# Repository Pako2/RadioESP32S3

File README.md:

# RadioESP32S3
## Introduction
&nbsp;&nbsp;&nbsp;&nbsp;Some time ago I published the [RadioESP32](https://github.com/Pako2/RadioESP32) project. It was intended exclusively for the basic ESP32 chips. I realized that it would be good to also try a variant with the more modern ESP32-S3 chip and this is the result. Since almost everything is identical to the original project, I will mainly emphasize the differences here.\
&nbsp;&nbsp;&nbsp;&nbsp;Complete project documentation can be found in the [UserGuide_EN.pdf](doc/UserGuide_EN.pdf) file.

## How to install
Experienced Tinkerers who have installed VS Code with PlatformIO supplement and normally use it probably do not need any other advice. Everything is described in the previous text. However, there may be some less experienced users who are interested in trying the project and do not need to make their own modifications. In this case, they can use pre-compiled binaries and install them in ESP32-S3 without VS Code/Platformio.
The procedure is as follows (valid only to Windows users):
1. The default assumption is that the development kit is connected to the USB port of your computer and you know the number of (virtual) COM port. Suppose it's a *COM10*. Use the connector marked *COM* (not *USB*) on the development kit.
2. Download the latest [RadioESP32S3_binaries.zip](https://github.com/Pako2/RadioESP32S3/releases/latest/download/RadioESP32S3_binaries.zip) and unpack the ZIP file to some suitable (work) folder.
3. In the selected folder, the **bin** folder appears that contains everything you need.
4. Open the command line window (**cmd.exe**) so that you are in the above folder **bin**.
5. Enter the **flash.bat** command. The following offer should appear:

6. Select the desired firmware version (ie press the appropriate number) and then press Enter.
7. You will then be prompted to enter a COM port. Write the corresponding name (by example in point **1** it would be *COM10*) and press Enter.
8. There should be installed the necessary SW into ESP32.
9. After completion you can continue according to the **First start** chapter.

<ins>Note:</ins>\
The *withota* and *withotanodisp* versions are intended for production use, while the *noota* and *nootanodisp* versions are intended primarily for the development phase (as they allow comfortable editing of web server files). However, there is nothing to prevent the *noota* and *nootanodisp* versions from being used for production use as well.

## First start
When the device is started for the first time, it runs in default settings and in AP mode. On the PC, connect to the **RadioESP32S3** network and in the browser to the address **192.168.4.1**. A web page should appear through which the device settings need to be made.

## Design of the device
The circuit diagram and printed circuit board were created using the Eagle design system.
### Wiring diagram

### Printed circuit board

## Choice of components
The basis of the design is the development kit "ESP32-S3-DevKitC-1" (shorter wider version). The board must have at least 8MB of flash memory and 4MB of PSRAM memory.

## Choice of GPIO
I designed and used a PCB where the assignment of GPIOs for various functions is therefore fixed. But this is not fixed in the software. In fact, it is the opposite, most GPIOs can be selected by the user, so it should be easy to use a different connection than the PCB I designed.
However, there are two exceptions:
1. Display connection - this must be set in the *platformio.ini* file before compilation.
2. Selection of ADC channel for battery measurement (I chose channel adc1-6, which corresponds to GPIO 7)

<ins>Note:</ins>\
In the original design with the ESP32 base chip, there is a third exception - connecting an SD card in SD_MMC mode. Fortunately, there is no such exception here, because in this case (ESP32-S3 chip) any GPIO pin can be used. This is of course a huge advantage, because the problems that were with the ESP32 base chip (there GPIO2, which is one of the bootstrapping pins, had to be used) have disappeared.

## Assembled board
Finally, you can see a few pictures of the printed circuit board completely assembled and including the installed subboards (ESP32 development kit and DAC). I also added one photo of the finished radio (without the cover).

### License
The code parts written by the author of the **RadioESP32S3** project are licensed under [GPL-3.0](LICENSE), 3rd party libraries that are used by this project are licensed under different license schemes, please check them out as well.

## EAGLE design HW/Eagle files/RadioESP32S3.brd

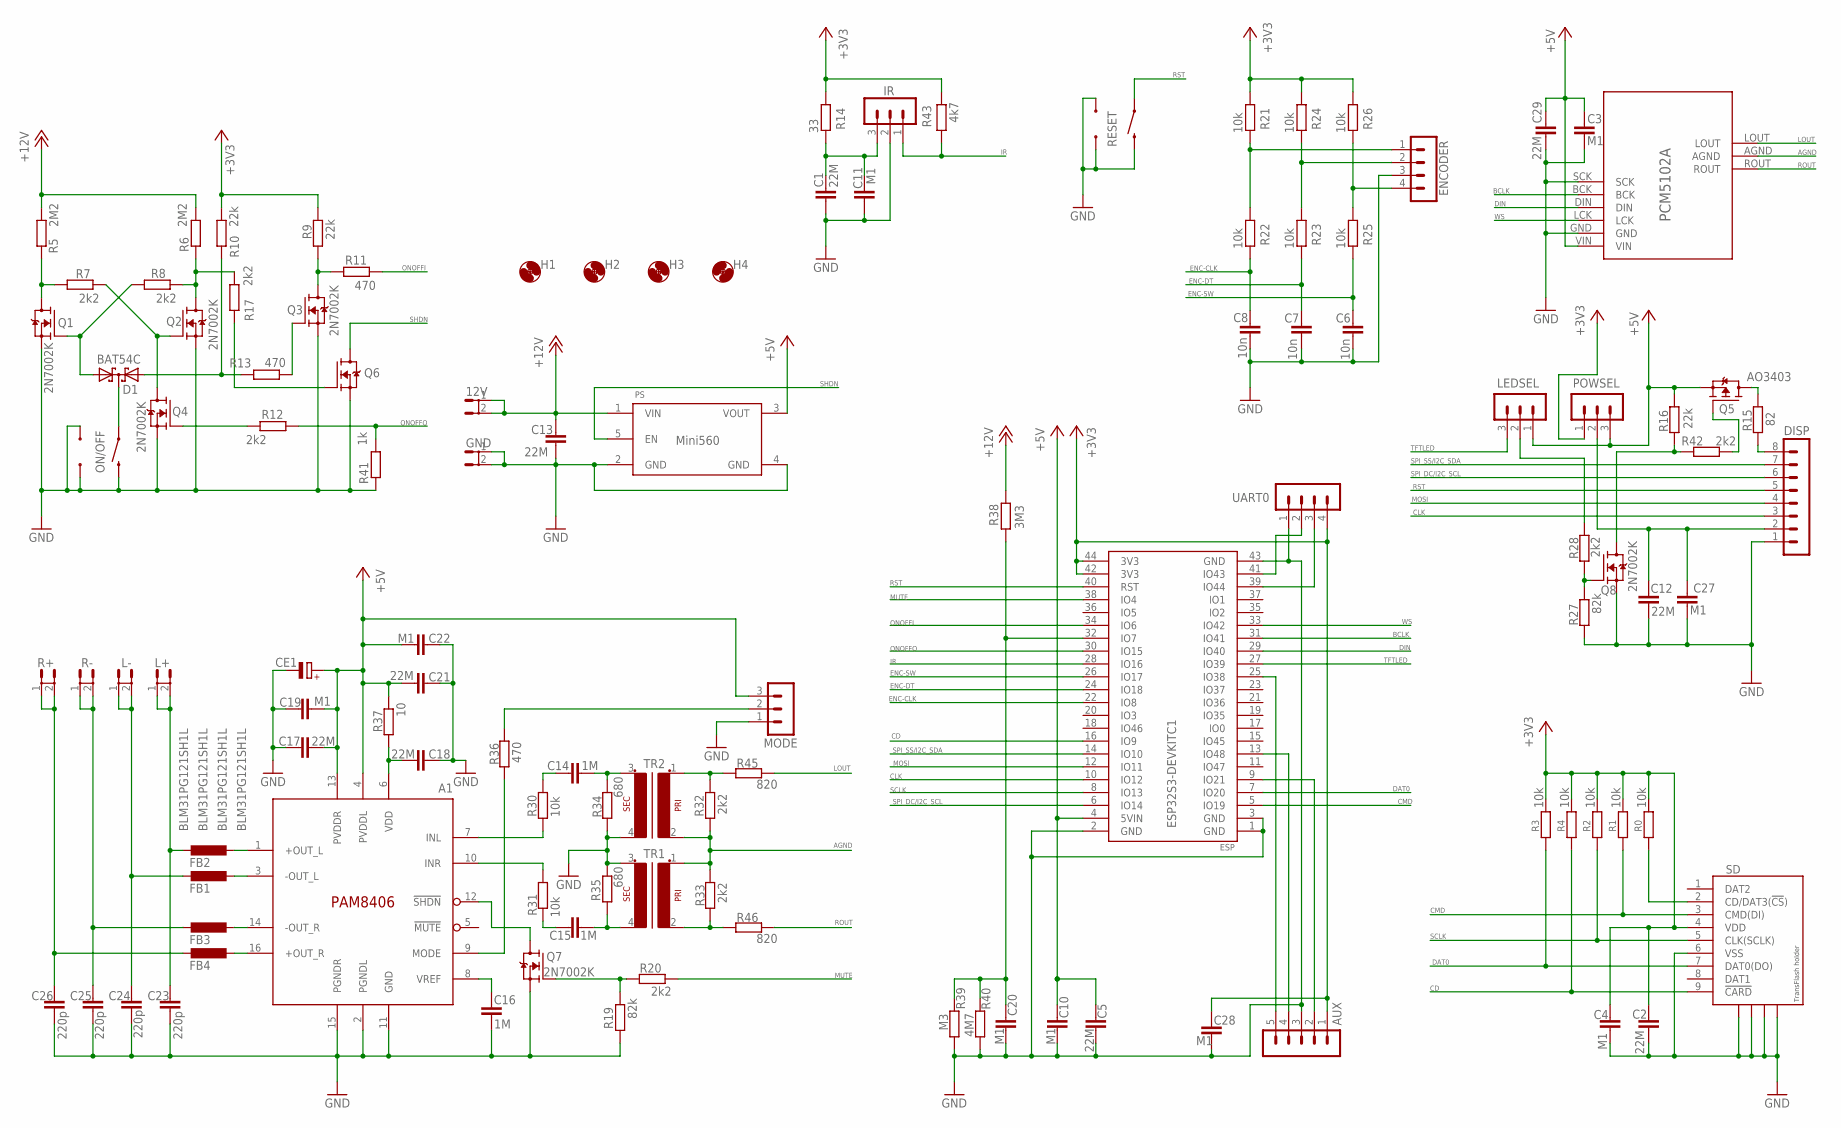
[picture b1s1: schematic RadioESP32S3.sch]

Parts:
12V: FASTON; FASTON4.8
A1: PAM8406; SOP-16
AUX: CON-LSTB_MA05-108; CON-LSTB_MA05-1-NS08
C1, C2, C5, C12, C13, C17, C18, C21, C29: 22M; C1206K
C3, C4, C10, C11, C19, C20, C22, C27, C28: M1; C0805
C6, C7, C8: 10n; C0805
C14, C15, C16: 1M; C1206K
C23, C24, C25, C26: 220p; C0805
CE1: CPOL; E5-10.5
D1: BAT54C; SOT23
DISP: CON-LSTB_MA08-108; CON-LSTB-MA08-1-NS08
ENCODER: CON-LSTB_MA04-108; CON-LSTB_MA04-1-NS08
ESP: ESP32S3-DEVKITC1
FB1, FB2, FB3, FB4: BLM31PG121SH1L; C1206K
GND: FASTON; FASTON4.8
H1, H2, H3, H4: MOUNT-HOLE3.0; 3,0
IR: CON-LSTB_MA03-108; CON-LSTB_MA03-1-NS08
L+: FASTON; FASTON4.8
L-: FASTON; FASTON4.8
LEDSEL: CON-LSTB_MA03-108; CON-LSTB_MA03-1-NS08
MODE: CON-LSTB_MA03-108; CON-LSTB_MA03-1-NS08
ON/OFF: MOMENTARY-SWITCH-SPST1; TACTILE_SWITCH_ANGLE-NS1
PCM5102A: PCM5102A_MODULE
POWSEL: CON-LSTB_MA03-108; CON-LSTB_MA03-1-NS08
PS: MINI560EXT; MINI560-NS-EXT
Q1, Q2, Q3, Q4, Q6, Q7, Q8: 2N7002K; TRANSISTOR-FET_SOT23
Q5: AO3403; SOT23
R0, R1, R2, R3, R4, R21, R22, R23, R24, R25, R26, R30, R31: 10k; R0805
R5, R6: 2M2; R0805
R7, R8, R12, R17, R20, R28, R32, R33, R42: 2k2; R0805
R9, R10, R16: 22k; R0805
R11, R13, R36: 470; R0805
R14: 33; R0805
R15: 82; R1206
R19, R27: 82k; R0805
R34, R35: 680; R0805
R37: 10; R0805
R38: 3M3; R0805
R39: M3; R0805
R40: 4M7; R0805
R41: 1k; R0805
R43: 4k7; R0805
R45, R46: 820; R0805
R+: FASTON; FASTON4.8
R-: FASTON; FASTON4.8
RESET: MOMENTARY-SWITCH-SPST1; TACTILE_SWITCH_ANGLE-NS1
SD: SD-MMC_TF-HOLDER; SD-MMC_TF-PULL
TR1, TR2: AUDIOTRAFONS2; AUDIOTRAFO_2-NS
UART0: CON-LSTB_MA04-108; CON-LSTB_MA04-1-NS08

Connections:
+3V3: AUX.1, C2.2, C4.2, C28.2, ESP.42 (3V3), ESP.44 (3V3), POWSEL.1, R0.2, R1.2, R2.2, R3.2, R4.2, R9.2, R10.2, R14.2, R21.2, R24.2, R26.2, R43.1, SD.4 (VDD), UART0.4 (5)
+5V: A1.4 (PVDDL), A1.13 (PVDDR), C3.1, C5.1, C10.1, C17.2, C19.2, C21.1, C22.1, C29.2, CE1.+, CE1.++ (+), ESP.4 (5VIN), LEDSEL.1, MODE.3, PCM5102A.VIN, POWSEL.3, PS.3 (VOUT), Q5.2 (S), R16.2, R37.1
+12V: 12V.1, 12V.2, C13.2, PS.1 (VIN), R5.2, R6.2, R38.2
AGND: PCM5102A.AGND, R32.1, R33.2, TR1.1, TR2.2
BCLK: ESP.31 (IO41), PCM5102A.BCK
CD: ESP.16 (IO9), R4.1, SD.9 (!CARD)
CLK: DISP.3, ESP.10 (IO12)
CMD: ESP.5 (IO19), R1.1, SD.3 (CMD(DI))
DAT0: ESP.7 (IO20), R3.1, SD.7 (DAT0(DO))
DIN: ESP.29 (IO40), PCM5102A.DIN
ENC-CLK: C8.1, ESP.22 (IO8), R22.1
ENC-DT: C7.1, ESP.24 (IO18), R23.1
ENC-SW: C6.1, ESP.26 (IO17), R25.1
GND: A1.2 (PGNDL), A1.11 (GND), A1.15 (PGNDR), AUX.3, C1.2, C2.1, C3.2, C4.1, C5.2, C6.2, C7.2, C8.2, C10.2, C11.2, C12.1, C13.1, C16.1, C17.1, C18.2, C19.1, C20.1, C21.2, C22.2, C23.1, C24.1, C25.1, C26.1, C27.2, C28.1, C29.1, CE1.-, DISP.1, ENCODER.3 (4), ESP.1 (GND), ESP.2 (GND), ESP.3 (GND), ESP.43 (GND), GND.1, GND.2, IR.2, MODE.1, ON/OFF.2, ON/OFF.A1, ON/OFF.A2, PCM5102A.GND, PCM5102A.SCK, PS.2 (GND), PS.4 (GND), Q1.2 (S), Q2.2 (S), Q3.2 (S), Q4.2 (S), Q6.2 (S), Q7.2 (S), Q8.2 (S), R19.2, R27.2, R34.1, R35.2, R39.1, R40.1, R41.1, RESET.2, RESET.A1, RESET.A2, SD.6 (VSS), SD.S1, SD.S2, SD.S3, SD.S4, TR1.3 (S1), TR2.4 (S2), UART0.1 (2)
IR: ESP.28 (IO16), IR.1, R43.2
LEDA: DISP.8, R15.1
LOUT: PCM5102A.LOUT, R45.2
MOSI: DISP.4, ESP.12 (IO11)
MUTE: ESP.38 (IO4), R20.1
N31: D1.2 (A2), R10.1, R13.2
unnamed: ESP.39 (IO44), UART0.3 (4)
unnamed: ESP.41 (IO43), UART0.2 (3)
unnamed: C14.1, R34.2, TR2.3 (S1)
unnamed: C15.2, R35.1, TR1.4 (S2)
unnamed: C14.2, R30.2
unnamed: A1.7 (INL), R30.1
unnamed: C15.1, R31.2
unnamed: A1.10 (INR), R31.1
unnamed: C1.1, C11.1, IR.3, R14.1
unnamed: Q2.3 (D), R6.1, R8.1, R17.1
unnamed: Q7.1 (G), R19.1, R20.2
unnamed: R0.1, SD.2 (CD/DAT3(!CS!))
unnamed: Q3.1 (G), R13.1
unnamed: Q1.3 (D), R5.1, R7.2
unnamed: Q5.1 (G), R42.1
unnamed: D1.3 (CC), ON/OFF.1
unnamed: Q2.1 (G), Q4.3 (D), R7.1
unnamed: D1.1 (A1), Q1.1 (G), R8.2
unnamed: Q4.1 (G), R12.2
unnamed: AUX.4, ESP.13 (IO48)
unnamed: Q3.3 (D), R9.1, R11.2
unnamed: AUX.2, ESP.9 (IO21)
unnamed: C12.2, C27.1, DISP.2, POWSEL.2
unnamed: R32.2, R45.1, TR2.1
unnamed: A1.8 (VREF), C16.2
unnamed: A1.12 (!SHDN), Q7.3 (D)
unnamed: A1.9 (MODE), R36.1
unnamed: MODE.2, R36.2
unnamed: C23.2, FB2.2, L+.1, L+.2
unnamed: R33.1, R46.1, TR1.2
unnamed: C25.2, FB3.2, R-.1, R-.2
unnamed: C26.2, FB4.2, R+.1, R+.2
unnamed: A1.1 (+OUT_L), FB2.1
unnamed: A1.3 (-OUT_L), FB1.1
unnamed: A1.14 (-OUT_R), FB3.1
unnamed: A1.16 (+OUT_R), FB4.1
unnamed: Q5.3 (D), R15.2
unnamed: Q8.3 (D), R16.1, R42.2
unnamed: C20.2, ESP.32 (IO7), R38.1, R39.2, R40.2
unnamed: Q6.1 (G), R17.2
unnamed: C24.2, FB1.2, L-.1, L-.2
unnamed: ENCODER.4 (5), R25.2, R26.1
unnamed: ENCODER.2 (3), R23.2, R24.1
unnamed: ENCODER.1 (2), R21.1, R22.2
unnamed: Q8.1 (G), R27.1, R28.1
ONOFFI: ESP.34 (IO6), R11.1
ONOFFO: ESP.30 (IO15), R12.1, R41.2
ROUT: PCM5102A.ROUT, R46.2
RST: DISP.5, ESP.40 (RST), RESET.1
SCLK: ESP.8 (IO13), R2.1, SD.5 (CLK(SCLK))
SHDN: PS.5 (EN), Q6.3 (D)
SPI_DC/I2C_SCL: DISP.6, ESP.6 (IO14)
SPI_SS/I2C_SDA: DISP.7, ESP.14 (IO10)
TFTG: LEDSEL.2, R28.2
TFTLED: ESP.27 (IO39), LEDSEL.3
VDD: A1.6 (VDD), C18.1, R37.2
WS: ESP.33 (IO42), PCM5102A.LCK
XDCS: AUX.5, ESP.25 (IO38)

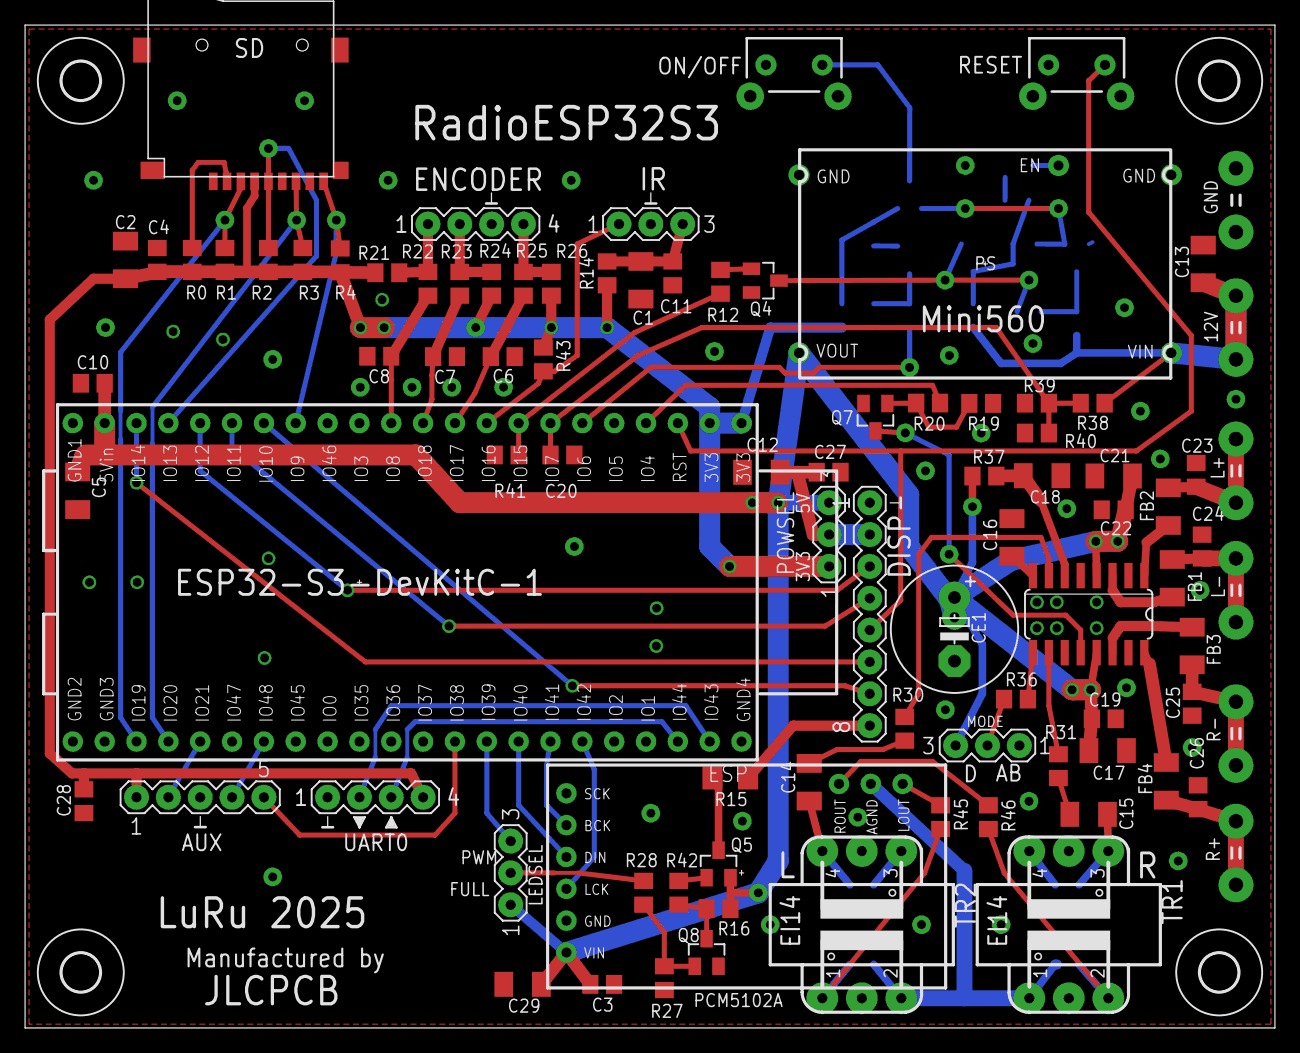
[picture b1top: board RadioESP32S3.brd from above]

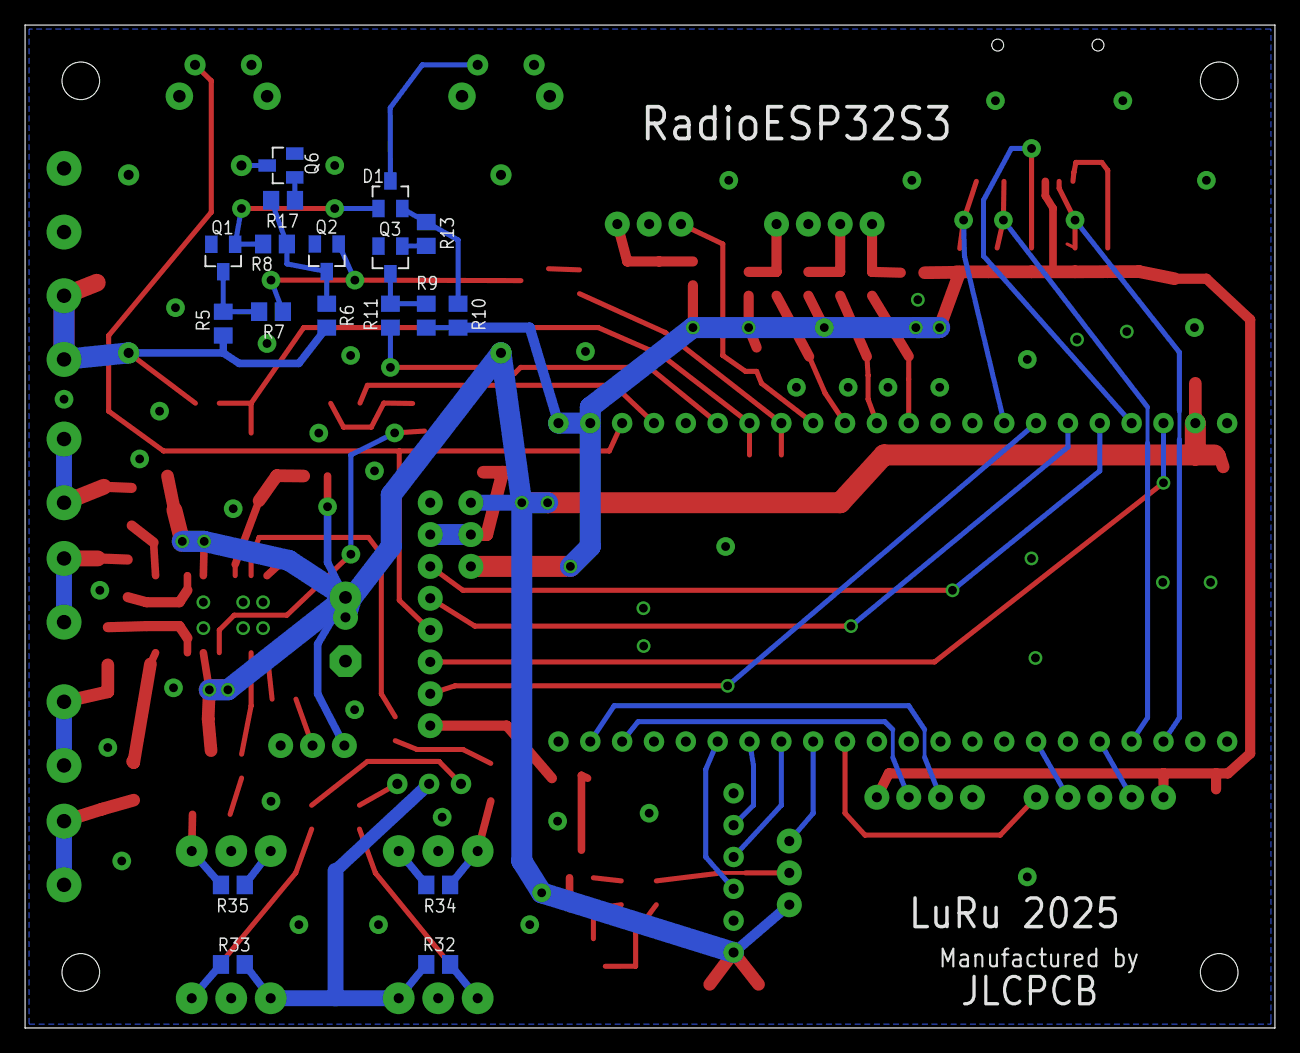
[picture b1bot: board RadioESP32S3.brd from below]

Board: 2 copper layers, 99.7 x 80.0 mm, 113 parts (18 on the bottom side), 78 nets.

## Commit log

2025-05-22 1.0.7 - first public version
